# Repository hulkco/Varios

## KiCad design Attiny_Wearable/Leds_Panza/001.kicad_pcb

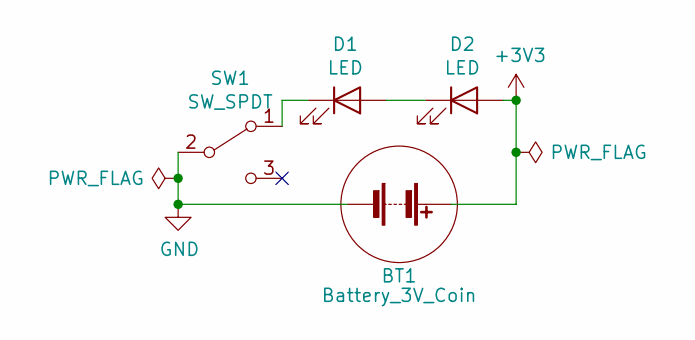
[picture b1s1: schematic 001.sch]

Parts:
BT1: Battery_3V_Coin; S8211R
D1, D2: LED; LED_D5.0mm_FlatTop
SW1: SW_SPDT; SW_SPDT_PCM12

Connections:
+3V3: BT1.1 (+), D2.2 (A)
GND: BT1.2 (-), SW1.2 (B)
unnamed: D1.1 (K), SW1.1 (A)
unnamed: D1.2 (A), D2.1 (K)

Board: 2 copper layers, 5 parts (4 on the bottom side), 4 nets, no tracks yet.

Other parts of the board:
Ref**: Val**; cody

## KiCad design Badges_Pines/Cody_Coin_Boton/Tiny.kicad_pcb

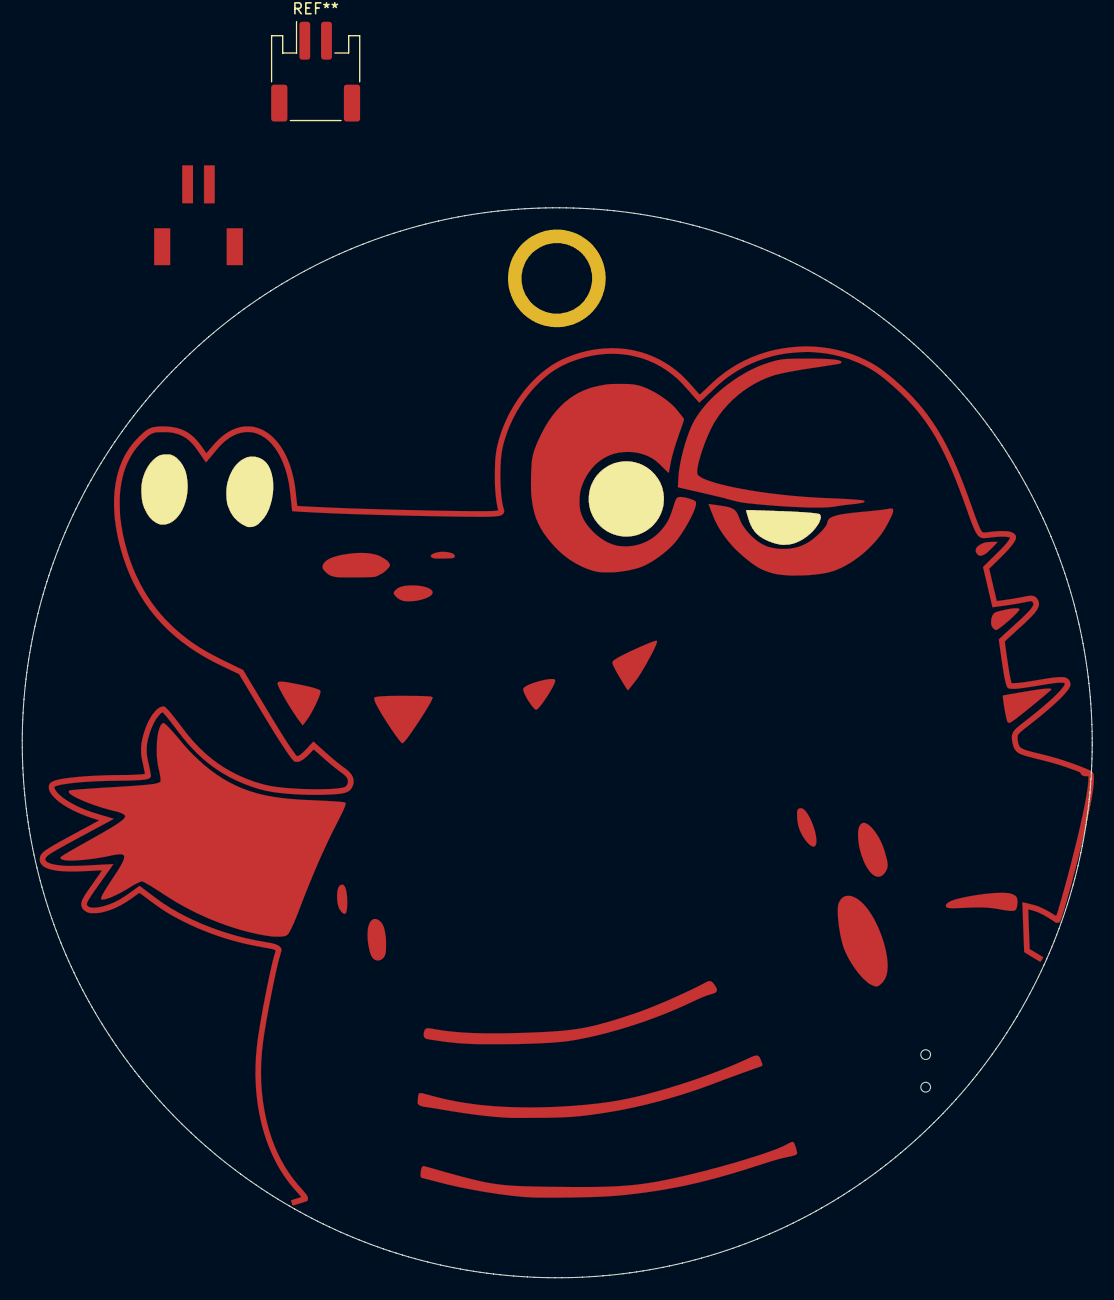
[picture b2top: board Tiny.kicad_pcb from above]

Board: 2 copper layers, 98.6 x 98.6 mm, 21 parts (0 on the bottom side), 9 nets, no tracks yet.

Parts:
BT1: Battery_3V_Coin; S8211R
D1, D2, D3, D4, D5, D6, D7, D8, D9, D10, D11, D12: LED_Small_ALT; LED_1206_3216Metric_Pad1.42x1.75mm_HandSolder
H1: MountingHole; MountingHole_Codi_Coin
J2: S2B-PH-SM4-TB; JST-S2B-PH-SM4-TB
JP5: PINHD-1X6; PogoPinSocket_2x03_P2.54mm
R1: R; R_1206_3216Metric_Pad1.42x1.75mm_HandSolder
SW1: SW_Push; SW_SPST_B3U-1000P
SW2: SW_Push_SPDT; SW_SPDT_PCM12
U1: ATtiny85-20SU; SOIJ-8_5.3x5.3mm_P1.27mm
U2: Codi_Coin; Cody_Coin

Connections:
+3V0: BT1.1, JP5.1, U1.8
/RST: JP5.3, U1.1
/T0: D5.2, D6.1, D11.2, D12.1, JP5.4, U1.5
/T1: D3.2, D4.1, D9.2, D10.1, JP5.5, U1.6
/T2: D1.2, D2.1, D7.2, D8.1, JP5.6, SW1.2, U1.7
/T3: D1.1, D2.2, D3.1, D4.2, D5.1, D6.2, U1.2
/T4: D7.1, D8.2, D9.1, D10.2, D11.1, D12.2, U1.3
GND: BT1.2, JP5.2, R1.2, SW2.1, SW2.2, U1.4
unnamed: R1.1, SW1.1

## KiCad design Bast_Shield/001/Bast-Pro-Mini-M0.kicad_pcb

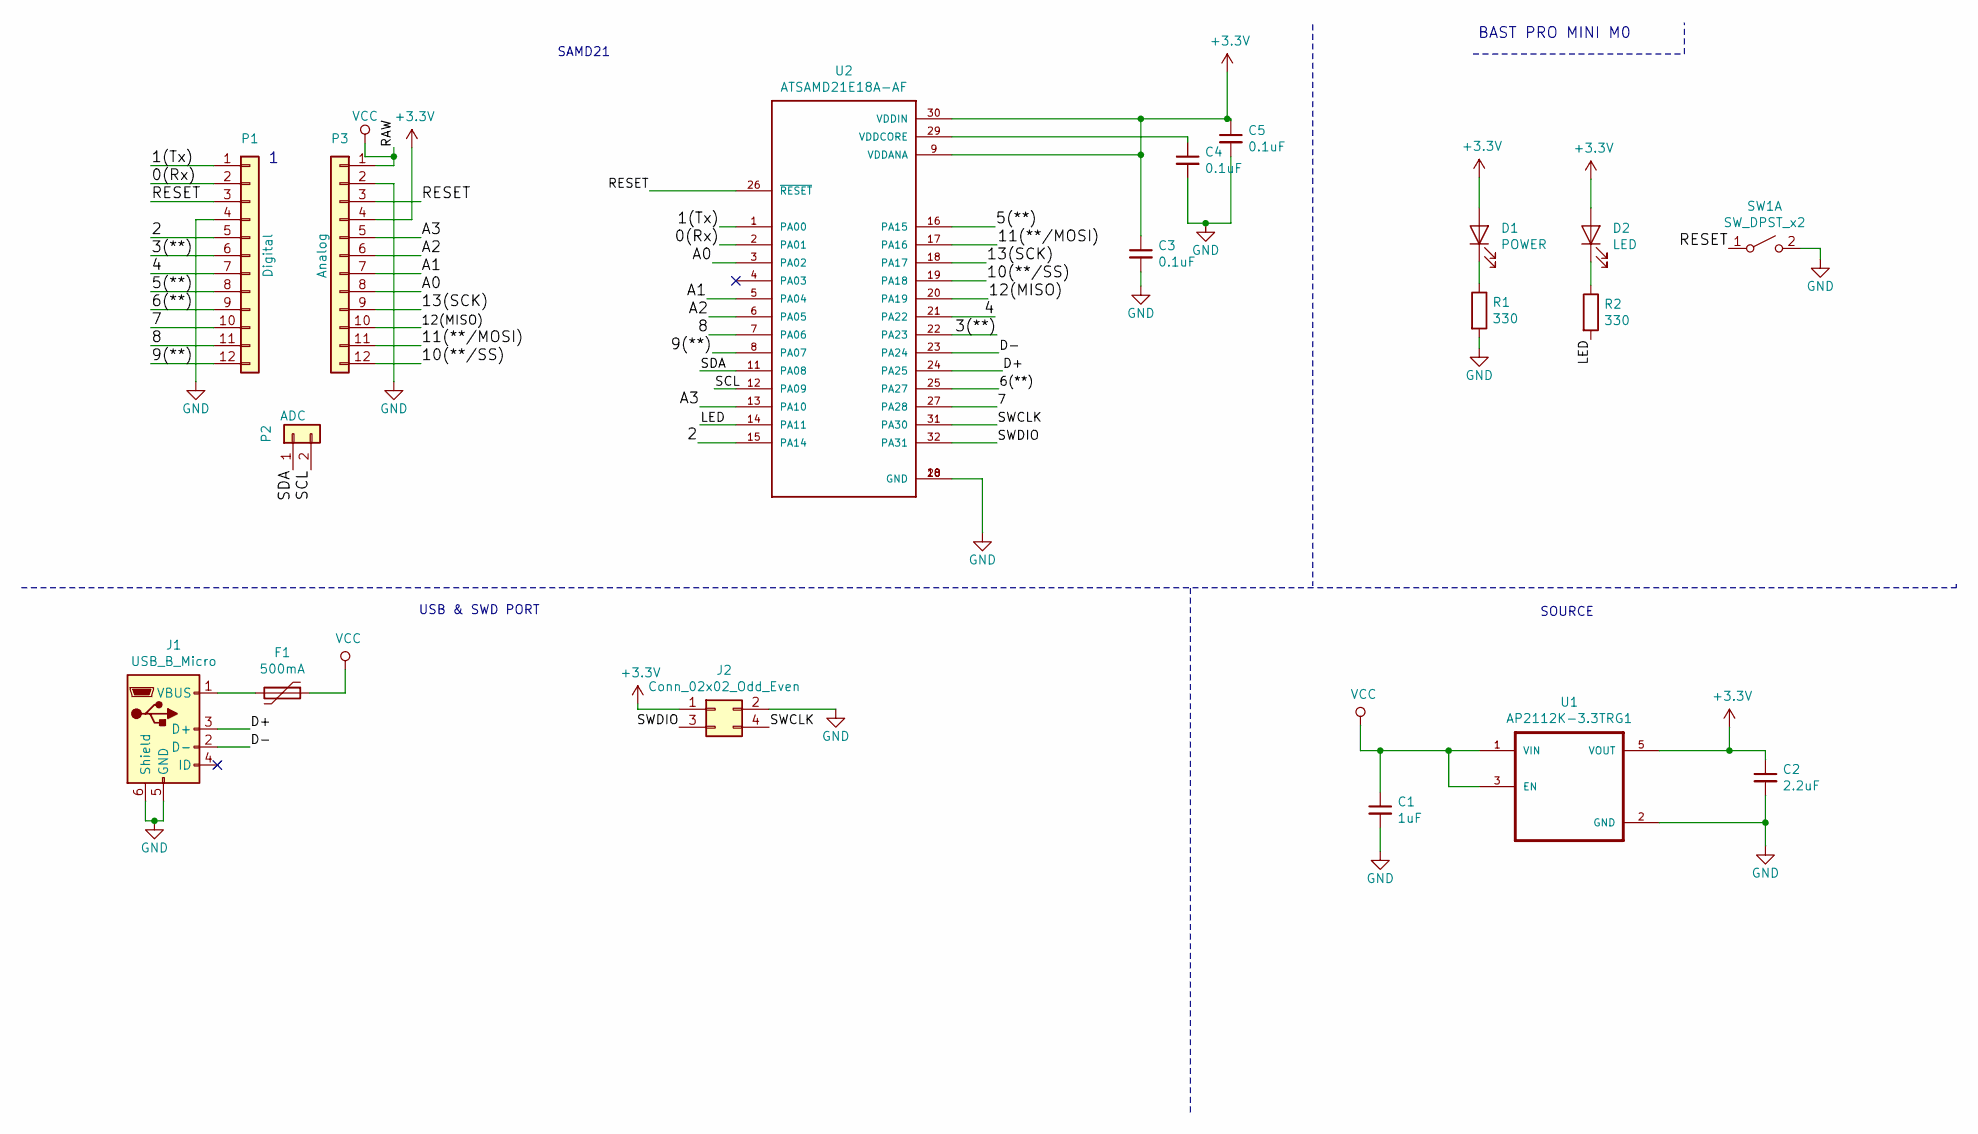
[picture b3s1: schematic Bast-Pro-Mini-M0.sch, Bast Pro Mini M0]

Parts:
C1: 1uF; C_0603_1608Metric_Pad1.05x0.95mm_HandSolder
C2: 2.2uF; C_0603_1608Metric_Pad1.05x0.95mm_HandSolder
C3, C4, C5: 0.1uF; C_0603_1608Metric_Pad1.05x0.95mm_HandSolder
D1: POWER; LED_0805_2012Metric_Pad1.15x1.40mm_HandSolder
D2: LED; LED_0805_2012Metric_Pad1.15x1.40mm_HandSolder
F1: 500mA; Fuse_0805_2012Metric_Pad1.15x1.40mm_HandSolder
J1: USB_B_Micro; USB_Micro-B_Wuerth_629105150521
J2: Conn_02x02_Odd_Even; PinHeader_2x02_P2.54mm_Vertical_SMD
P1: Digital; PinHeader_1x12_P2.54mm_Vertical
P2: ADC; PinHeader_1x02_P2.54mm_Vertical
P3: Analog; PinHeader_1x12_P2.54mm_Vertical
R1, R2: 330; R_0603_1608Metric_Pad1.05x0.95mm_HandSolder
SW1: SW_DPST_x2; SW_SPST_TL3342
U1: AP2112K-3.3TRG1; SOT-23-5
U2: ATSAMD21E18A-AF; TQFP-32_7x7mm_P0.8mm

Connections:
+3V3: C2.1, C3.1, C5.1, D1.2 (A), D2.2 (A), J2.1, P3.4, U1.5 (VOUT), U2.9 (VDDANA), U2.30 (VDDIN)
/0(Rx): P1.2, U2.2 (PA01)
/1(Tx): P1.1, U2.1 (PA00)
/2: P1.5, U2.15 (PA14)
/3(**): P1.6, U2.22 (PA23)
/4: P1.7, U2.21 (PA22)
/5(**): P1.8, U2.16 (PA15)
/6(**): P1.9, U2.25 (PA27)
/7: P1.10, U2.27 (PA28)
/8: P1.11, U2.7 (PA06)
/9(**): P1.12, U2.8 (PA07)
/10(**/SS): P3.12, U2.19 (PA18)
/11(**/MOSI): P3.11, U2.17 (PA16)
/12(MISO): P3.10, U2.20 (PA19)
/13(SCK): P3.9, U2.18 (PA17)
/A0: P3.8, U2.3 (PA02)
/A1: P3.7, U2.5 (PA04)
/A2: P3.6, U2.6 (PA05)
/A3: P3.5, U2.13 (PA10)
/D+: J1.3 (D+), U2.24 (PA25); also elsewhere on the board
/D-: J1.2 (D-), U2.23 (PA24); also elsewhere on the board
/LED: R2.2, U2.14 (PA11)
/RESET: P1.3, P3.3, SW1.1 (A), U2.26 (~RESET~)
/SCL: P2.2, U2.12 (PA09)
/SDA: P2.1, U2.11 (PA08)
/SWCLK: J2.4, U2.31 (PA30)
/SWDIO: J2.3, U2.32 (PA31)
GND: C1.2, C2.2, C3.2, C4.2, C5.2, J1.5 (GND), J1.6 (Shield), J2.2, P1.4, P3.2, R1.2, SW1.2 (B), U1.2 (GND), U2.10 (GND), U2.28 (GND); also elsewhere on the board
unnamed: C4.1, U2.29 (VDDCORE)
unnamed: D1.1 (K), R1.1
unnamed: D2.1 (K), R2.1
unnamed 31: F1.2, J1.1 (VBUS); also elsewhere on the board
unnamed 32: J1.4 (ID); also elsewhere on the board
VCC: C1.1, F1.1, P3.1, U1.1 (VIN), U1.3 (EN)

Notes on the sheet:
BAST PRO MINI M0
SAMD21
SOURCE
USB & SWD PORT

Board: 2 copper layers, 19 parts (5 on the bottom side), 34 nets, no tracks yet.

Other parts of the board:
J1#2: USB_B_Micro; USB_Micro-B_Wuerth_629105150521

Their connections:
/D+: J1#2.3; also elsewhere on the board
/D-: J1#2.2; also elsewhere on the board
GND: J1#2.5, J1#2.6; also elsewhere on the board
unnamed 31: J1#2.1; also elsewhere on the board
unnamed 32: J1#2.4; also elsewhere on the board

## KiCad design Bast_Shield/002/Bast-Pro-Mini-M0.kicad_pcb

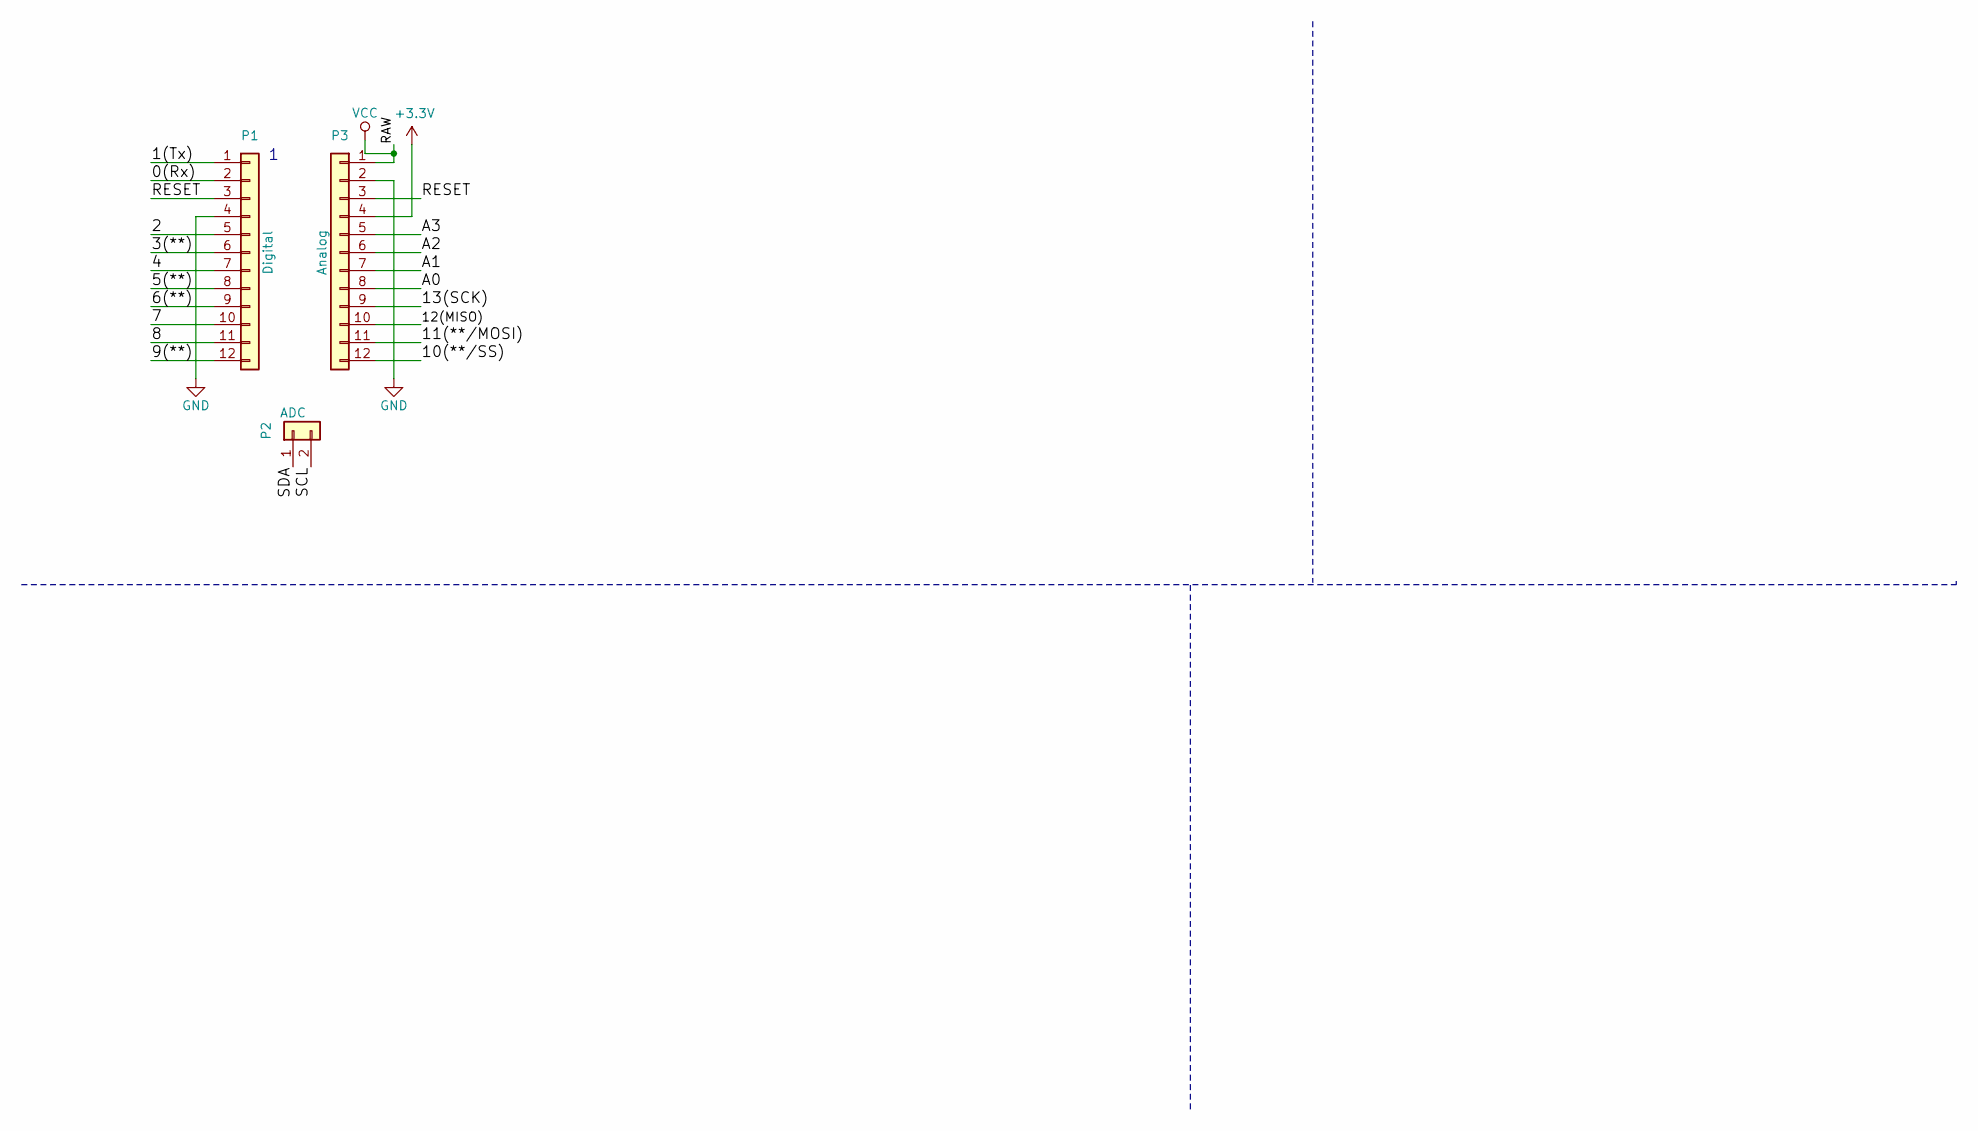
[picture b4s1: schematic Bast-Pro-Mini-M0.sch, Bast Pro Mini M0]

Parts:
P1: Digital; PinSocket_1x12_P2.54mm_Vertical_SMD_Pin1Left
P2: ADC; PinSocket_1x02_P2.54mm_Vertical_SMD_Pin1Left
P3: Analog; PinSocket_1x12_P2.54mm_Vertical_SMD_Pin1Right

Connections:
+3V3: P3.4
/0(Rx): P1.2
/1(Tx): P1.1
/2: P1.5
/3(**): P1.6
/4: P1.7
/5(**): P1.8
/6(**): P1.9
/7: P1.10
/8: P1.11
/9(**): P1.12
/10(**/SS): P3.12
/11(**/MOSI): P3.11
/12(MISO): P3.10
/13(SCK): P3.9
/A0: P3.8
/A1: P3.7
/A2: P3.6
/A3: P3.5
/RESET: P1.3, P3.3
/SCL: P2.2
/SDA: P2.1
GND: P1.4, P3.2
VCC: P3.1

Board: 2 copper layers, 3 parts (0 on the bottom side), 2 nets, no tracks yet.

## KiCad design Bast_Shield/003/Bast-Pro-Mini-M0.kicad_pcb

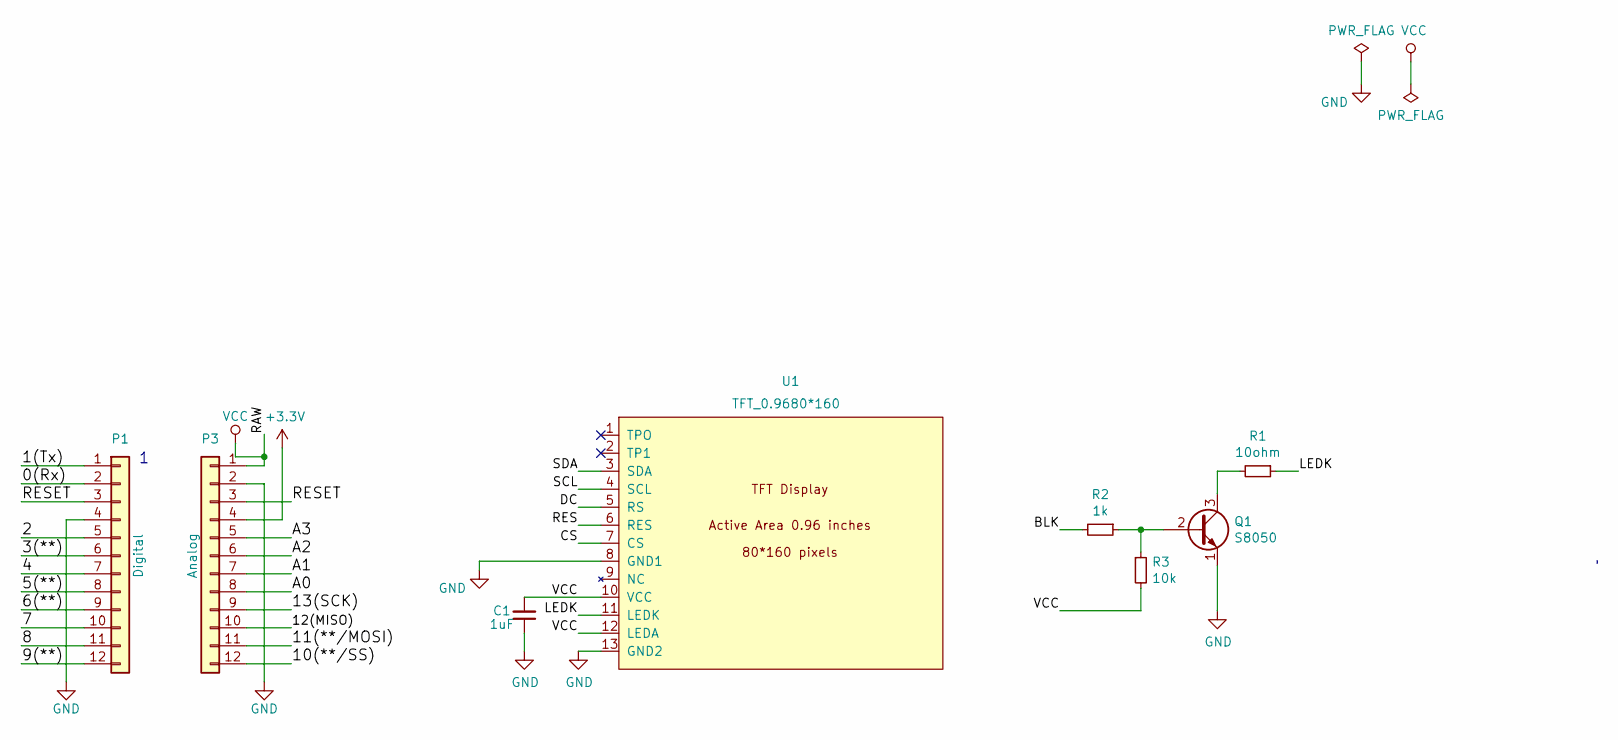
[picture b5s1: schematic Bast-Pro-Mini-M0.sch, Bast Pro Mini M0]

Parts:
C1: 1uF; C_0805_2012Metric_Pad1.15x1.40mm_HandSolder
P1: Digital; PinSocket_1x12_P2.54mm_Vertical_SMD_Pin1Left
P3: Analog; PinSocket_1x12_P2.54mm_Vertical_SMD_Pin1Right
Q1: S8050; SOT-23
R1: 10ohm; R_0805_2012Metric_Pad1.15x1.40mm_HandSolder
R2: 1k; R_0805_2012Metric_Pad1.15x1.40mm_HandSolder
R3: 10k; R_0805_2012Metric_Pad1.15x1.40mm_HandSolder
U1: TFT_0.9680*160; TFT_0.96_SPI

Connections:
+3V3: P3.4
/0(Rx): P1.2
/1(Tx): P1.1
/2: P1.5
/3(**): P1.6
/4: P1.7
/5(**): P1.8
/6(**): P1.9
/7: P1.10
/8: P1.11
/9(**): P1.12
/10(**/SS): P3.12
/11(**/MOSI): P3.11
/12(MISO): P3.10
/13(SCK): P3.9
/A0: P3.8
/A1: P3.7
/A2: P3.6
/A3: P3.5
/BLK: R2.2
/CS: U1.7 (CS)
/DC: U1.5 (RS)
/LEDK: R1.1, U1.11 (LEDK)
/RES: U1.6 (RES)
/RESET: P1.3, P3.3
/SCL: U1.4 (SCL)
/SDA: U1.3 (SDA)
GND: C1.1, P1.4, P3.2, Q1.1 (E), U1.8 (GND1), U1.13 (GND2)
unnamed: Q1.2 (B), R2.1, R3.1
unnamed: Q1.3 (C), R1.2
VCC: C1.2, P3.1, R3.2, U1.10 (VCC), U1.12 (LEDA)

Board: 2 copper layers, 10 parts (2 on the bottom side), 6 nets, no tracks yet.

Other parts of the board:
svg2mod: G***; Bast_5
svg2mod#2: G***; firma
